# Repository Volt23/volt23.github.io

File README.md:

# volt23.github.io
# yo
# portfolio1

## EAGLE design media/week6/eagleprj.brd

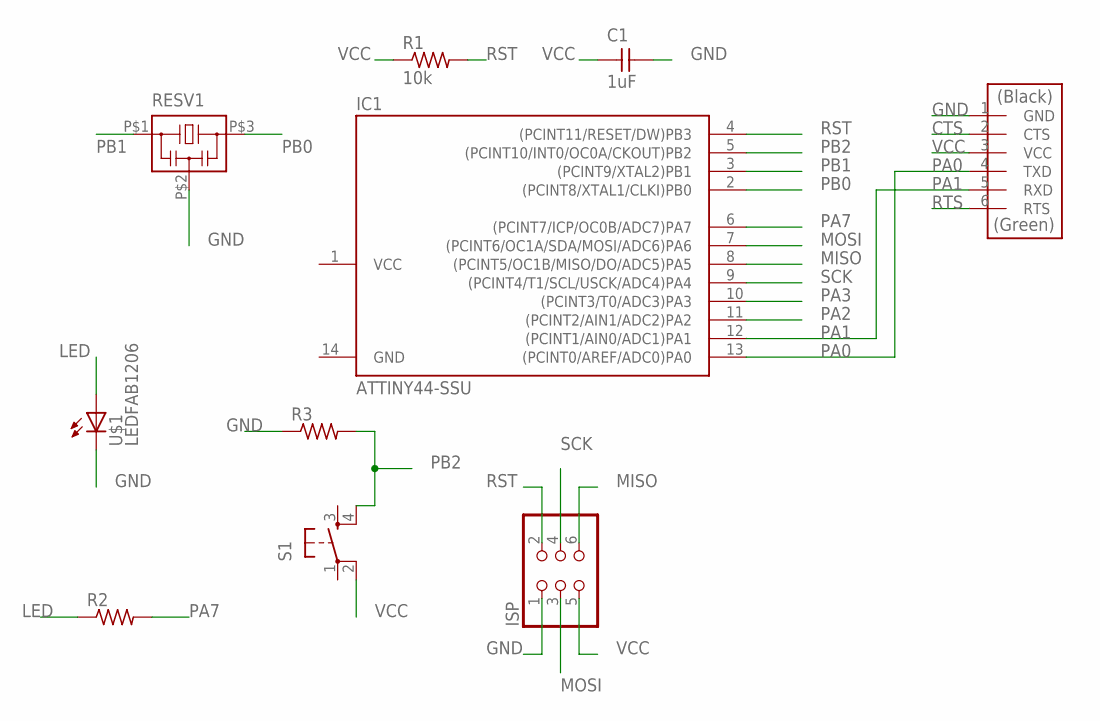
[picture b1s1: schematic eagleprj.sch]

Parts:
C1: 1uF; C1206FAB
IC1: ATTINY44-SSU; SOIC14
ISP: PINHD-2X3-SMD; 2X03SMD
R1: 10k; R1206FAB
R2, R3: RES-US1206FAB; R1206FAB
RESV1: RESONATOR-VOLT; VOLT
S1: 6MM_SWITCH6MM_SWITCH; 6MM_SWITCH
U$1: LEDFAB1206; LED1206FAB
U$2: FTDI-SMD-HEADER; 1X06SMD

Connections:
CTS: U$2.2 (CTS)
GND: C1.2, IC1.14 (GND), ISP.1, R3.1, RESV1.P$2 (2), U$1.2 (C), U$2.1 (GND)
LED: R2.1, U$1.1 (A)
MISO: IC1.8 ((PCINT5/OC1B/MISO/DO/ADC5)PA5), ISP.6
MOSI: IC1.7 ((PCINT6/OC1A/SDA/MOSI/ADC6)PA6), ISP.3
PA0: IC1.13 ((PCINT0/AREF/ADC0)PA0), U$2.4 (TXD)
PA1: IC1.12 ((PCINT1/AIN0/ADC1)PA1), U$2.5 (RXD)
PA2: IC1.11 ((PCINT2/AIN1/ADC2)PA2)
PA3: IC1.10 ((PCINT3/T0/ADC3)PA3)
PA7: IC1.6 ((PCINT7/ICP/OC0B/ADC7)PA7), R2.2
PB0: IC1.2 ((PCINT8/XTAL1/CLKI)PB0), RESV1.P$3 (3)
PB1: IC1.3 ((PCINT9/XTAL2)PB1), RESV1.P$1 (1)
PB2: IC1.5 ((PCINT10/INT0/OC0A/CKOUT)PB2), R3.2, S1.4 (S1)
RST: IC1.4 ((PCINT11/RESET/DW)PB3), ISP.2, R1.2
RTS: U$2.6 (RTS)
SCK: IC1.9 ((PCINT4/T1/SCL/USCK/ADC4)PA4), ISP.4
VCC: C1.1, IC1.1 (VCC), ISP.5, R1.1, S1.2 (P1), U$2.3 (VCC)

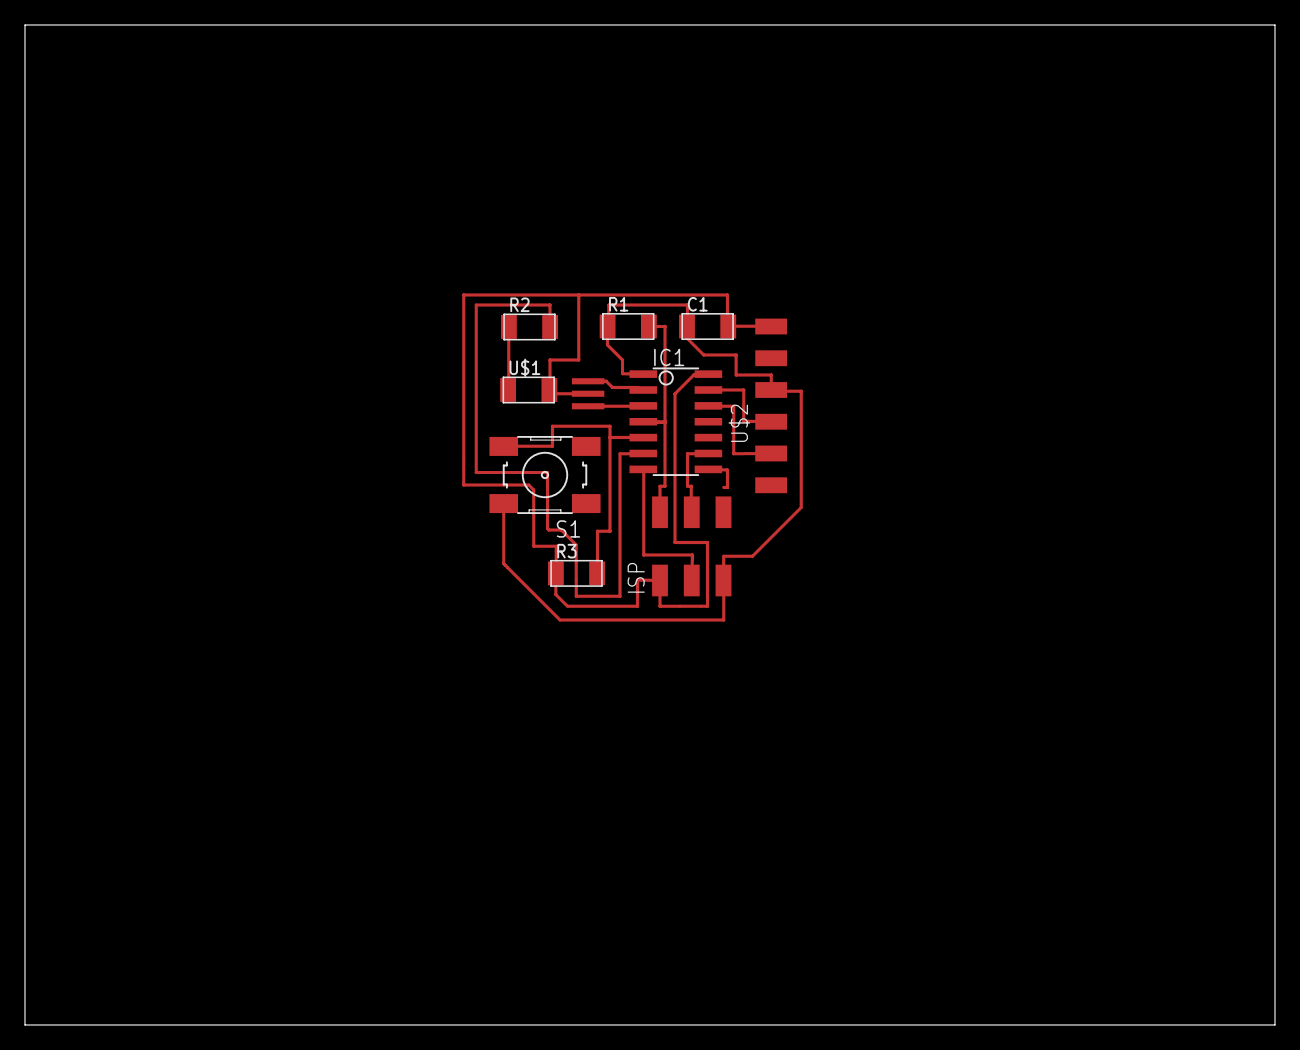
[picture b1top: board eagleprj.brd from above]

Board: 2 copper layers, 100.0 x 80.0 mm, 10 parts (0 on the bottom side), 13 nets.

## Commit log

2016-04-22 yo world commit
2016-04-23 web-app structure: gulp(browser-sync, sass, pug, uncss, autoprefixer) bower (susy, mappy breakpoints, typi)
2016-04-26 homepage structure
2016-05-23 website prototype
2016-05-24 added weeks
2016-05-24 changed text
2016-05-24 added text
2016-05-24 prova
2016-05-24 prova2
2016-05-24 provaprova
2016-05-24 master branch
2016-05-24 test finale
2016-05-24 master?
2016-05-24 links color
2016-05-24 intro text home
2016-05-24 added lines weeks index
2016-05-27 updated nav
2016-09-06 sperem
2016-09-07 corrected text
2016-11-13 update2
2016-11-18 huge upgrade
2016-11-18 fixed folders
2016-11-19 improved layout and media queries
2016-11-19 changed mobile margins
2016-11-19 menu mobile fixed margins
2016-11-20 uploaded prjs and graphic
2016-11-21 update portfolio
2016-12-02 update color
2018-11-04 v1.0
2018-11-04 fix hover
2020-04-17 gitignore update
2020-04-17 m9 update
2020-04-17 correzioni
2020-04-19 link fabacademy
2020-04-20 m900 update
2020-04-20 m900 3d altare
2020-04-20 typo
2020-04-20 date
2020-04-20 venchi update
2025-04-01 hide body content via css display none
